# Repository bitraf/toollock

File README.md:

# TheLock
Electronic lock connected via wireless (Wi-Fi) and MQTT using [MsgFlo](https://msgflo.org).
The lock is intended to enforce 'checking out' and 'checking in' portable tools in a shared workshop environment.

It makes it possible to:

* Know whether a tool is currently in its station
* Checking for neccesary safety course before allowing usage
* Holding people responsible when equipment is not get returned or broken

Each lock has a key with a matching key pattern. The key is physically attached to the tool using a wire.
An optical sensor detects that the right key is used. IR leds normally light through, only a matching key will fully block light.

The key and lock can be CNC-milled, lasercut or 3d-printed.

## Status
**Proof of concept**

* July 2017: Functional prototype was built during 2-day hackathon
* First production version planned for October 2017

## Bill of Materials

[Google Doc](https://docs.google.com/spreadsheets/d/1zNnj4h8AQoaYpxoNCeb7HHqZF6n6yWtV7tDY7eSM0z4/edit?usp=sharing)

* Microcontroller - ESP8266 or similar. We used a Wemos D1 board.
* actuator - we used a solenoid that is rated for 12V (it actually actuates at about 7V, but slowly), it draws about 0.3 - 0.7 A. Alternatives:
[1](https://www.banggood.com/12V-24V-Electronic-Door-Lock-Rfid-Access-Control-for-Cabinet-Drawer-p-1011146.html)
[2](https://www.banggood.com/12V-DC-Cabinet-Door-Drawer-Electric-Lock-Assembly-Solenoid-Lock-27x29x18mm-p-1048590.html)
* mosfet - we used a IPP055N03L
* resistor - a 10k ohm resistor for pulldown on the control signal
* power supply - a 12V DC power supply for the actuator / solenoid
* IR led 0805, 120deg. [Kingbright kp-2012f3c](http://no.farnell.com/kingbright/kp-2012f3c/led-ir-0805-940nm/dp/2290432)
* IR phototransistor 0805, 120 deg. [Kingbright kp-2012p3c](http://no.farnell.com/kingbright/kp-2012p3c/phototransistor-0805-940nm/dp/2290434)

https://wiki.wemos.cc/products:d1:d1_mini
https://github.com/esp8266/esp8266-wiki/wiki/Pin-definition

## Setup firmware

* Install Arduino libraries [PubsubClient](https://github.com/knolleary/pubsubclient) and [Msgflo](https://github.com/msgflo/msgflo-arduino)
* Setup wifi connection: Add a file `Config.h` defining parameters `WIFI_SSID` and `WIFI_PASSWORD`
* Configure MQTT details in the sketch

## TODO

v1.0: First fabricated version

* Electronics: Switch to a standard transmissive detector, PCB mounted.
* Mechanics: Update to vertical PCB orientation, check connections
* Produce initial 4 locks
* Mechanics: Add a casing/box for 4-8 locks. Securely wall/table mountable.

## License
MIT

## Made by

[einsmein](https://github.com/einsmein), [tingox](https://github.com/tingox) and [jonnor](https://github.com/jonnor)

## State machine

## Electronics

Developed in KiCAD.

## Mechanics

Developed in FreeCAD.

SIG: gnd+in
PWR: 12v+gnd
OUT: 12v+out

IN
GND
12v
12v
OUT

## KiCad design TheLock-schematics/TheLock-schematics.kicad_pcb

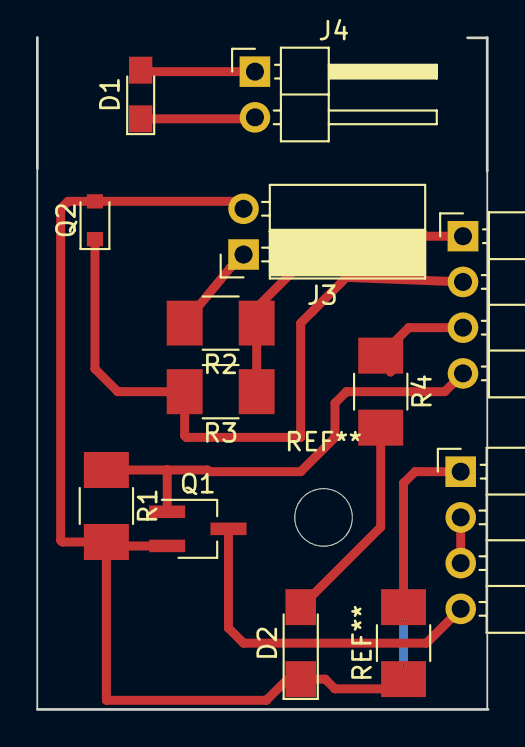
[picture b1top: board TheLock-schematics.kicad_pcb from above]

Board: 2 copper layers, 25.0 x 37.3 mm, 12 parts (0 on the bottom side), 11 nets.

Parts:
D1: IR LED; LED_0805_HandSoldering
D2: LED; LED_1206_HandSoldering
J1: CONN_SIGNAL; Pin_Header_Angled_1x04_Pitch2.54mm
J2: CONN_POWER; Pin_Header_Angled_1x04_Pitch2.54mm
J3: CONN_IRBOARD; Socket_Strip_Angled_1x02_Pitch2.54mm
J4: CONN_IRLED; Pin_Header_Angled_1x02_Pitch2.54mm
Q1: PMV20XNE; SOT-23W_Handsoldering
Q2: IR PHOTOTRANS; D_0805
R1: 10k; R_1210_HandSoldering
R2: 47; R_1210_HandSoldering
R3: 18k; R_1210_HandSoldering
R4: R; R_1210_HandSoldering

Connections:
+3V3: J1.1, R2.1, R3.1
GNDPWR: D2.1, J2.1, J3.2, Q1.2, Q2.2, R1.2
unnamed: D1.1, J4.2
unnamed: D1.2, J4.1
unnamed: D2.2, R4.2
unnamed: J3.1, R2.2
keypresent: J1.2, Q2.1, R3.2
solenoid+: J2.2, J2.3
solenoid-: J2.4, Q1.3
status: J1.3, R4.1
unlock: J1.4, Q1.1, R1.1

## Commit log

2017-07-01 initialize
2017-07-01 Connected with mqtt
2017-07-01 added initial readme file, describing the project
2017-07-01 Added readme
2017-07-01 Cleanup
2017-07-01 Fixed readme
2017-07-01 added initial schematics (in KiCad) for the circuit.
2017-07-01 added the missing components to the readme file
2017-07-01 corrected list formatting in README.md file
2017-07-02 Fixed the code for MC and added fake button code
2017-07-02 added unlock py script
2017-07-02 updated Kicad schematics
2017-07-02 Added light sensor
2017-07-02 Added lock init state
2017-07-04 schematics: Add optical key sensor
2017-07-04 doc: Add statemachine diagram
2017-07-04 doc: Add some pictures
2017-07-06 Add mechanical model
2017-09-16 firmware: Make testable
2017-09-16 Travis: Initial setup, run tests
2017-09-16 firmware: Rename to toollock
2017-09-16 README: Update TODO
2017-09-16 Specify C++11
2017-09-16 README: Put a link to BOM google doc
2017-09-16 README: Status update
2017-09-16 mechanics: Update to cabinet lock
2017-09-28 mechanics: Update to fit received solenoids
    Was a bit larger than specified, had to be moved 5mm in
2017-10-02 firmware: Update to unlock-on-high
2017-10-02 firmware: Send state on outport
2017-10-02 firmware: Avoid always sending state, only unlock in takeTool
2017-10-02 firmware: Rename locked to toolPresent
2017-10-02 firmware: Fix compile error in tests
2017-10-02 firmware: Wait until timeout also when tool is taken
    Otherwise the lock may trigger again before the key
    has cleared completely
2017-10-02 firmware: Validate input and report errors
2017-10-02 firmware: Fix wrong portname for error
2017-10-02 firmware: Run 4 lock instances
    Requires msgflo/msgflo-arudino#14
2017-10-03 electronics: Update to the lock driver board
    Will have header connectors, so that 3-4 of them
    can be connected to a single ESP8266 module
2017-10-03 electronics: Rough layout of lock board
2017-10-04 firmware: Add status LED, 3x locks per micro
2017-10-05 electronics: PCB layout and mechanics should conform now
    IR phototrans and LED should be positioned OK
    PCB size and attachment should be roughly OK
2017-10-05 .gitignore: Ignore intermediates for statemachine diagram
2017-10-08 electronics: Update to better accommodate LED
2017-10-08 mechanics: Forgot update
2017-10-09 mechanics: Initial code for generating key/lock pairs
2017-10-09 mechanics: Also add text to generated keys
2017-10-09 mechanics: Group generated keygeometry
2017-12-05 README: More precise TODO
2018-02-19 README: Update
